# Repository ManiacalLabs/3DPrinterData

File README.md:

# 3DPrinterData
A place to store files, scripts, profiles, etc. for any of our 3D printers.

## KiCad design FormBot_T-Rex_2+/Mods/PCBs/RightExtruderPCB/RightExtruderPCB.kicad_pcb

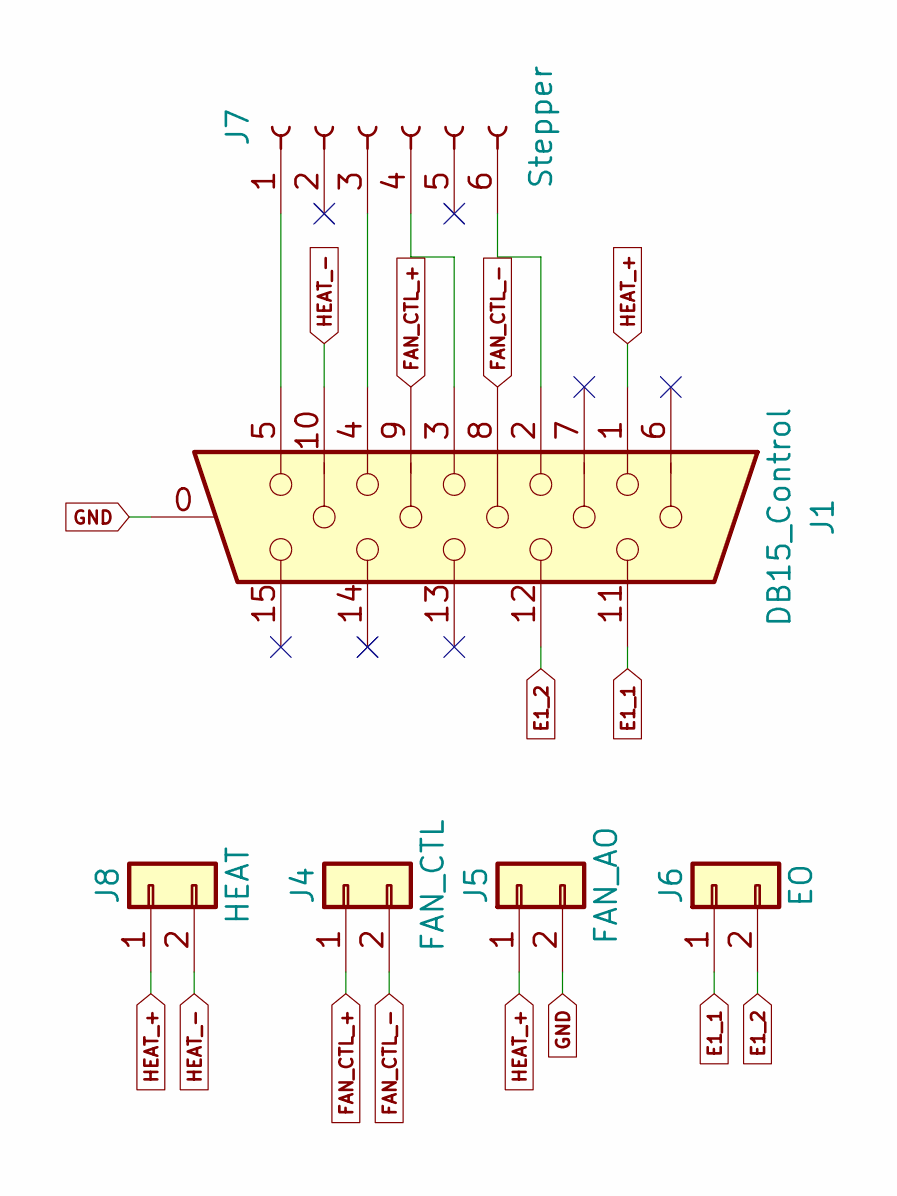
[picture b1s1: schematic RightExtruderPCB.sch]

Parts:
J1: DB15_Control; VGA_Female
J4: FAN_CTL; JST_XH_B02B-XH-A_02x2.50mm_Straight
J5: FAN_AO; JST_XH_B02B-XH-A_02x2.50mm_Straight
J6: EO; JST_XH_B02B-XH-A_02x2.50mm_Straight
J7: Stepper; Pin_Header_Straight_1x06_Pitch2.00mm
J8: HEAT; TerminalBlock_bornier-2_P5.08mm

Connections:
E1_1: J1.11, J6.1
E1_2: J1.12, J6.2
FAN_CTL_+: J1.9, J4.1
FAN_CTL_-: J1.8, J4.2
GND: J1.0, J5.2
HEAT_+: J1.1, J5.1, J8.1
HEAT_-: J1.10, J8.2
unnamed: J1.2, J7.6
unnamed: J1.3, J7.4
unnamed: J1.4, J7.3
unnamed: J1.5, J7.1

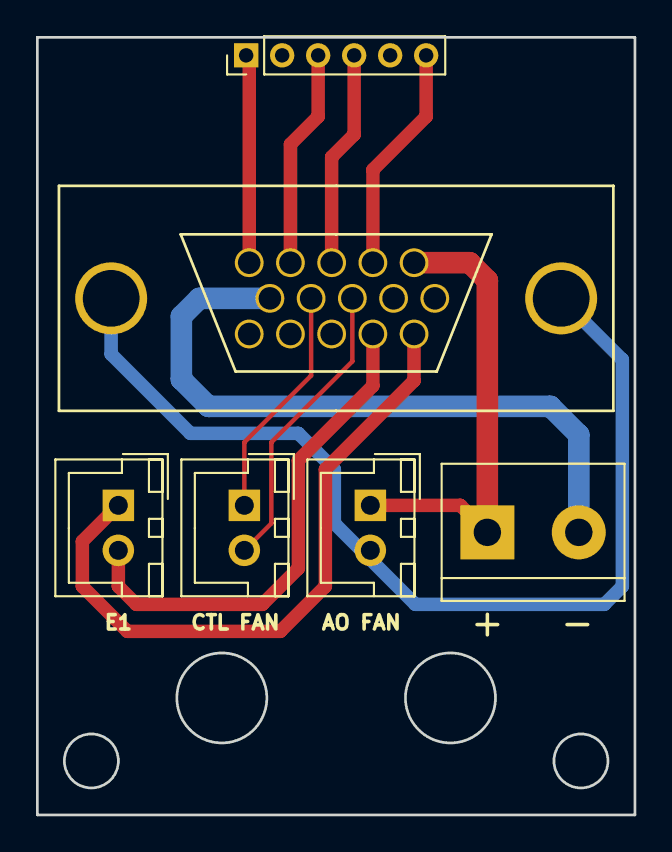
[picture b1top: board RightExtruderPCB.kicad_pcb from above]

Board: 2 copper layers, 33.2 x 43.2 mm, 6 parts (0 on the bottom side), 11 nets.

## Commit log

2017-10-21 Adding a few initial details and models
2017-10-22 Adding profiles and original manuals
2017-10-22 Renamed profile
2017-10-22 Adding Y axis motor listing
2017-10-22 new Mods dir and bed controller holder step file
2017-11-04 Updating profiles
2017-11-04 add SSR Mod
2017-11-04 Adding dual extruder profile
2017-11-05 update single profile
2017-11-07 update dual profile
2017-11-08 Added fan shrouds
2017-11-19 whole bunch of new stuff
2017-11-23 Added HT hotend settings
2017-11-29 Update right tool profile
2017-11-29 update right profile with final settings
2017-12-10 Updated profiles and starting PCB for extruders
2017-12-18 Adding right extruder PCB
2017-12-18 update BOM
2018-01-24 Update profiles
2019-01-26 Adding T-Rex 3.0
2019-03-31 Update profiles. Add T3 source code
2019-03-31 Add T3 S3D profiles
2019-03-31 Adding motor cover mod
2019-05-03 Add volcano profiles
2019-05-07 Add volcano mods
2019-05-07 Update 1.2mm profile
2019-05-07 Adjust Z height
2019-05-07 Add readme
2019-05-07 Add Select Mini Pro files
2020-07-11 Adding daedalus
